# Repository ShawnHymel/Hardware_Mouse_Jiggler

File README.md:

Hardware Mouse Jiggler
======================

This is a simple prank that causes the target's mouse pointer to jump, jitter, or move every few seconds. Simply plug it into their computer and walk away.

Full instructions on making this USB dongle can be found at [https://learn.sparkfun.com/tutorials/tech-prank-hardware-mouse-jiggler](https://learn.sparkfun.com/tutorials/tech-prank-hardware-mouse-jiggler).

The 3D Printed case design can be found at [https://www.tinkercad.com/things/0UCciUgonUd](https://www.tinkercad.com/things/0UCciUgonUd).

License Information
-------------------
The hardware is released under [Creative Commons BY 4.0](https://creativecommons.org/licenses/by/4.0/).
All other code is open source so please feel free to do anything you want with it; you buy me a beer if you use this and we meet someday ([Beerware license](http://en.wikipedia.org/wiki/Beerware)).

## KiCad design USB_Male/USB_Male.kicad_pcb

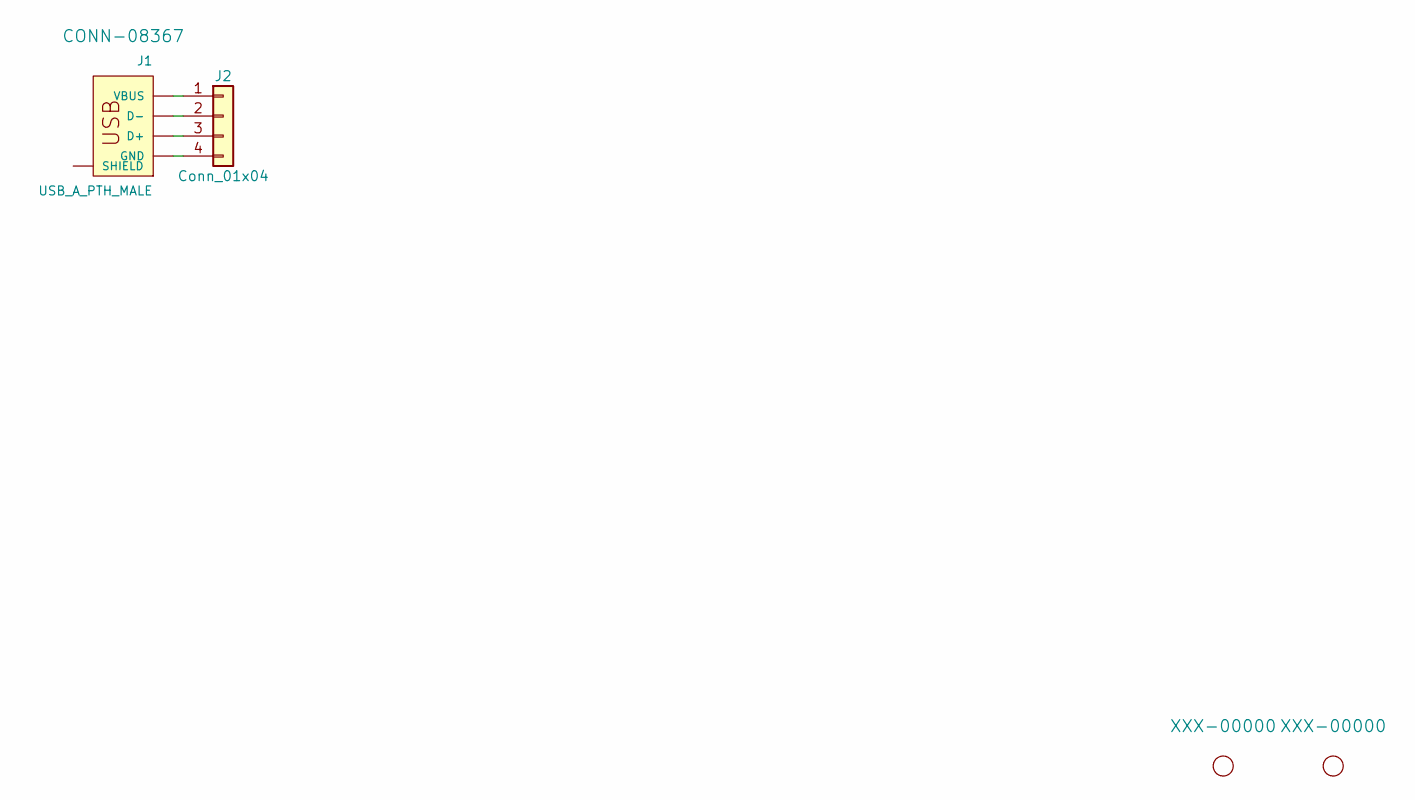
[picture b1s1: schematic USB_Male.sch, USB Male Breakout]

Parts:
H1, H2: STAND-OFF
J1: USB_A_PTH_MALE; USB-A-H
J2: Conn_01x04; Pin_Header_Straight_1x04_Pitch2.54mm

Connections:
unnamed: J1.D+, J2.3
unnamed: J1.D-, J2.2
unnamed: J1.GND, J2.4
unnamed: J1.VBUS, J2.1

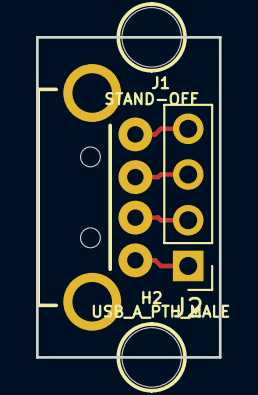
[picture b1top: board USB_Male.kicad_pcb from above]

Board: 2 copper layers, 10.2 x 17.8 mm, 4 parts (0 on the bottom side), 4 nets.

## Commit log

2018-03-06 Added USB breakout board files
2018-03-06 Added 3D printing files and Arduino code
2018-03-06 Added README

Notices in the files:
USB_Male/USB_Male.sch:
https://creativecommons.org/licenses/by-sa/4.0
License: CC BY-SA 4.0
